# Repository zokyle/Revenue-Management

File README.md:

# Revenue-Management

Two independent FastAPI applications share this repository and its Python
dependencies:

| App | Directory | Run | What it does |
|-----|-----------|-----|--------------|
| Hotel revenue management | `app/` | `uvicorn app.main:app --reload` | demand forecasting, dynamic pricing, overbooking, PMS integrations |
| **Caddie** - golf strategy agent | `golf/` | `uvicorn golf.main:app --reload --port 8001` | learns your golf game from logged rounds and builds hole-by-hole strategies for any course, with the goal of breaking 80 |

```bash
pip install -r requirements.txt
cp .env.example .env
python scripts/seed_golf.py      # demo golfer, course and 12 rounds for the golf app
python -m pytest -q              # both apps' test suites
```

See [`golf/README.md`](golf/README.md) for how the golf agent works (with
pictures and analogies), the data-collection workflow, and the API.

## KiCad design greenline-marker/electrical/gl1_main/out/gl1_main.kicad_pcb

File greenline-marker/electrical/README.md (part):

# GL-1 electrical package

Nothing in this directory has been built or measured. The boards exist as design scripts,
KiCad 7 files generated from them and fabrication data that passed KiCad's DRC. Several
land patterns and pin tables are PROVISIONAL (list below): **do not order boards before
those are checked against the manufacturers' drawings.**

**Revision E (E-EVT1), 2026-11-18.** Both boards are rebuilt on revision E of
`design/master_params.yaml` and `design/DESIGN_SPEC.md` (amendments E24 to E28, E35, E36). No
part moved and no net changed on the main board: it was routed again from nothing because the
stored routing's fingerprint covers the revision stamp, and the copper came out identical to
revision D (2570 segments, 278 vias, compared item by item; `gl1_main/LAYOUT_LOG.md`, section
"Revision E"). The cradle board is 1.0 mm thick instead of 1.6 mm (E36). Both builds end with
the mechanical package's import check and both exit 0.

Revised before that on 2026-11-18 after three independent reviews of the first layout. What
changed then is in `gl1_main/LAYOUT_LOG.md` and in the design files under "REVIEW FIX".

## What is here

| Path | What |
|---|---|
| `tools/` | the in-house toolchain "gleda" 0.4.0: netlist as code, KiCad 7 board, router, KiCad DRC as the judge, outputs. Read `tools/README.md`, at least "Limitations" |
| `gl1_main/gl1_main_design.py` | main board: parts, nets, pin map, mechanical contract (from `design/master_params.yaml`), placement, router options |
| `gl1_main/build_gl1_main.py` | one command: checks, spec-rule table, pin-map check, board, route, KiCad DRC, outputs, schematic, mechanical import, quality figures, review renders -> `gl1_main/out/` |
| `gl1_main/build_netlist.py` | the earlier stage without copper -> `gl1_main/netlist_out/` |
| `gl1_main/check_netlist_rules.py`, `check_pinmap.py`, `pinmap.json` | specification -> netlist table with seeded-defect self-test; pin map against ST's open pin data; the exported pin map (a copy is in `out/`) |
| `gl1_main/routing.json` | the stored routing (reused when the design fingerprint matches; audited again on every build) |
| `gl1_main/NETLIST_NOTES.md`, `LAYOUT_LOG.md` | every value with its calculation, departures, PROVISIONAL list; every routing attempt |
| `gl1_main/layout_quality.py`, `layout_review.py`, `silk_text.py` | figures measured on the copper (the second file: the measurements the reviewers made, repeated by every build); silkscreen legend helper |
| `gl1_cradle/` | the cradle board, same structure (`gl1_cradle_design.py`, `build_gl1_cradle.py`, `build_netlist.py`, `check_cradle_rules.py`, `CRADLE_NOTES.md`, `make_usb_footprint.py`, `gl1_cradle_fp.pretty/`); its build also ends with the mechanical import (`board_import.py --cradle`) |

In each `out/`: `<name>.kicad_pcb / .kicad_pro / .kicad_dru`, `fab/` (Gerber X2, Excellon,
`README.txt` with stack-up, finish, via tenting and plugging) and `<name>-fab.zip`,
`assembly/` (position file, BOM, `<name>-bom-status.csv`, README) and `<name>-assembly.zip`,
`schematic/` (PDF, PNG,
netlist round trip), `<name>-mechanical.json`, `<name>-netlist.json`, `<name>-board.step`,
`renders/` and `review/` (PNG of every copper layer and both assembly sides), `drc.json`,
`layout_quality.md`, `build_summary.json`, `spec_rules.md`, `mechanical_import.txt`,
`outputs.json` (every output file with size and SHA-256; the build completes it with the status
BOM, the extended assembly README and the final assembly zip and then compares every entry
with the file on disk); for the main board also `pinmap.json`, `pinmap_check.txt`.

**The status BOM has two status columns.** "Status" follows `docs/SOURCING.md`: VERIFIED = a US
source listing this exact part number was seen on the date in the last column (listed for
sale; not a stock promise), PROVISIONAL = everything else; it is copied from the numbered row of
`docs/sourcing.csv` (main-NN / cradle-NN) that has the line's references, and it is PROVISIONAL
when that row names another part number or does not exist (the build then prints a WARNING and
counts the line under "sourcing rows out of step with the BOM"; today 0 on both boards).
"Design evidence" is RESEARCH or PROVISIONAL: how well the pin table, land pattern and values
of the line are known (with a note). Today every part number on both boards is VERIFIED as a
listing, while 31 of 37 main-board lines and 6 of 7 cradle lines are PROVISIONAL in their
design data. A line can be ordered only when both allow it. The remaining columns are the
sourcing risk, the alternates the sourcing report names (actions A4 and A18) and the sourcing
row. The alternates are CANDIDATES: the column is headed "candidates, NOT approved", each cell
says VERIFIED or PROVISIONAL for itself, and no alternate has been approved by anybody (the
microcontroller's cell, for instance, names a different MCU whose pin compatibility is from memory).

## Rebuild

Use the system interpreter (it has KiCad's `pcbnew`). Run from the `greenline-marker`
directory. `PINDATA` is a directory outside the repository holding ST's two open pin data
files (`STM32U585RITx.xml`, `GPIO-STM32U5x_gpio_v1_0_Modes.xml`); without `--pindata` the
pin-map check is PARTIAL.

```
/usr/bin/python3 -B electrical/gl1_main/build_netlist.py --pindata PINDATA      # exit 0, about 25 s
/usr/bin/python3 -B electrical/gl1_main/build_gl1_main.py --pindata PINDATA     # exit 0, about 60 s with the stored routing
/usr/bin/python3 -B electrical/gl1_main/build_gl1_main.py --pindata PINDATA --reroute   # exit 0; routes from nothing: about 6.5 min (router 328 s)
/usr/bin/python3 -B electrical/gl1_cradle/build_netlist.py                      # exit 0, about 5 s
/usr/bin/python3 -B electrical/gl1_cradle/build_gl1_cradle.py                   # exit 0, about 30 s
/usr/bin/python3 -B electrical/gl1_main/update_notes.py --check                 # exit 0
/usr/bin/python3 -I -B electrical/gl1_main/check_pinmap.py --selftest --pindata PINDATA   # exit 0
/usr/bin/python3 -B electrical/gl1_main/check_netlist_rules.py --selftest       # exit 0 (49 seeded defects)
/usr/bin/python3 -B electrical/gl1_cradle/check_cradle_rules.py --selftest      # exit 0 (18 seeded defects)
(cd mechanical && python3 -B cad/board_import.py ../electrical/gl1_main/out/gl1_main-mechanical.json)             # exit 0
(cd mechanical && python3 -B cad/board_import.py --cradle ../electrical/gl1_cradle/out/gl1_cradle-mechanical.json)   # exit 0
(cd design && python3 check_parts_vs_board.py)                                  # exit 0: the YAML part lists match the board
```

Exit status of both board builds: **0** only if every stage passed, the mechanical import
included; **1** for anything else. (At revision D the main build exited 2 because the import
failed on J1; that special status is gone with its cause.) The mechanical stage also fails if
the import warns that the board file is stamped with another revision than the YAML or states
another height-limit zone. The stored routing is reused only when its fingerprint matches the
design and the router options; the fingerprint covers the whole design dictionary, so ANY edit
of a design file, a status note or fab note included, makes the next build route again (about
5.5 min; the router is deterministic, so unchanged geometry gives the same copper). Times are
from a 4-core machine.

## Result (2026-11-18, revision E-EVT1)

| | Main board `gl1_main` | Cradle `gl1_cradle` |
|---|---|---|
| Size, layers | D shape R 21.1 mm, flat at y 17.3; 4 layers, 0.8 mm, ENIG | 30 x 22 mm, 2 layers, **1.0 mm** (E36; 0.91 mm core), ENIG |
| Parts | 121 (104 on the BOM: 103 fitted + R14 not fitted; 11 bare-copper footprints; 6 fiducials) | 20 (13 on the BOM: 10 fitted + 3 spring pins not fitted; 1 bare; 6 fiducials) |
| Nets | 95 | 10 |
| Toolchain checks | 0 errors, 2 warnings (`plane_partial` twice: the GND pours round the crystal and over the photodiode, intended) | 0 errors, 0 warnings |
| Rule table | 66 rows: 62 as specified, 4 departures, 0 open, 0 workarounds, 0 failed; self-test 49 of 49 seeded defects | 15 rows: 14 as specified, 1 departure (USB-C land), 0 failed; self-test 18 of 18 |
| Routed | 306 of 306 connections, audit clean; 278 vias, 2570 segments, 2297.4 mm; identical to the revision D copper | 29 of 29; 9 vias, 126.8 mm |
| KiCad DRC | 0 errors, 0 unconnected; 2 warnings, both cosmetic silkscreen (`silk_over_copper`, `silk_overlap`); nothing excluded, no rule relaxed. One rule ADDED by the build (zone clearance, see toolchain limits) | 0 errors, 0 unconnected; 1 `silk_overlap` warning |
| Rules | board minimum 0.100 / 0.100 mm (track / clearance); classes Default 0.15 / 0.127 mm, Power 0.30 / 0.127 mm (neck 0.15), Fine 0.10 / 0.10 mm and CamPower 0.15 / 0.10 mm, the last two fine only inside the two fine areas (pad field + 5 mm, 175 mm2, 13 % of the board; E35); via 0.50 / 0.25 mm through; copper to edge 0.30, hole to copper 0.20; layer 2 solid GND; vias tented on BOTH sides, plugging from the bottom in the fab notes | board minimum 0.127 / 0.127 mm; classes Default 0.20 / 0.15 mm and Power 0.40 / 0.15 mm; via 0.50 / 0.25 mm; copper to edge 0.30, hole to copper 0.20; spring-pin holes 0.80 mm finished |
| Fine track | 218.3 mm of 0.100 mm track on 28 nets: F.Cu 133.7, In2.Cu 31.8, B.Cu 52.8 mm; all inside the fine areas, farthest 5.3 mm from a ball field. As E35 allows; the fab README names F.Cu, In2.Cu and B.Cu for 0.100 / 0.100 mm | none |
| Outputs | 35 files in `outputs.json`, each equal to the file on disk; plotted data verified against the model; BOM 37 lines (Status 37 VERIFIED; design evidence 31 PROVISIONAL, 6 RESEARCH); 103 position rows; schematic 8 sheets, round trip equal (95 nets, 400 pads) | 29 files; BOM 7 lines (Status 7 VERIFIED; design evidence 6 PROVISIONAL, 1 RESEARCH); schematic 3 sheets, round trip equal |
| Mechanical import | **passes, exit 0, no warning**: outline, hole and slot; 86 top-side parts 0.25 mm or more from the tub; J1 body box and anchor on the YAML (mouth y -17.3); the battery keep-out equals `battery.body` less the YAML notch; 18 bottom-side parts in the openings; 14 copper-only footprints by their own rules; 7 pads on the pin axes | **passes, exit 0** (`--cradle`, new at revision E): thickness 1.0, outline, four screw holes, seven pins on the pad row and on the modelled axes (4 fitted), receptacle on the modelled one, nothing else on the top face |

Main-board figures (`gl1_main/out/layout_quality.md`, measured by the build on the DRC'd board):

* Camera bus after the series arrays: 577 mm of track for 293 mm of spanning trees (x1.97),
  48 vias. This is WORSE than the first layout (449 mm).
* Camera data against PCLK, ball to MCU pad: left camera PCLK is the longest line (99.5 mm)
  and the data lines are 27 to 84 mm shorter (-589 to -188 ps at 7 ps/mm); right camera
  -9.7 to +77.5 mm (-68 to +542 ps); the longest line is 105 mm. The pixel clock is 12 MHz
  (period 83 ns), so the skew is under 1 % of a period; the copper is long all the same.
* Camera supply balls to the nearest capacitor of the net, along the copper: U2 DOVDD 9.9 mm,
  U2 AVDD 5.9 mm, U2 DVDD 4.2 mm, U3 DOVDD 5.0 mm, U3 AVDD 7.7 mm, U3 DVDD 7.1 mm.
* Smallest via-to-pad gap on the top side 0.100 mm (own net, vias tented), 0.134 mm to a pad
  of another net (rule 0.127). Smallest solder-mask web: top 0.150 mm (two IMU pads),
  bottom 0.360 mm. No via opening in either mask.
* Copper to the board edge (outline and the routed locating slot; rule 0.30): 0.325 mm routed
  (CAM_D3, at the slot), 0.355 mm pads (R4, at the slot). Copper to the wall of the drilled
  locating hole H1 (a separate rule, 0.20): 0.321 mm routed (CAM_D4), 0.795 mm pads. Earlier
  issues gave the 0.321 mm as an edge distance; the figures are now reported separately by
  `layout_quality.py`.
* Plane clearance: 0.200 mm to every foreign track and via on all four filled layers.
* Layer 3 (In2.Cu): V2V8 fill on 59.0 % of the board in 4 pieces, 461 mm of signal track;
  408 of 888 mm of bottom-layer track (46 %) has no In2 copper above it. It is a supply fill
  and a routing layer, not a plane. Layer 2: GND fill 86.0 %, one piece, no track.
* IMU: no copper in the top-layer rule area under the body, no via within 0.35 mm of the
  body outline; a CP1_MCU track clips the corner of the body outline by 0.03 mm; 12.3 mm or
  more from every regulator, 26 mm from the charger. U4 stands at 90 degrees (see "What the
  firmware must take from this board").
* Crystal: 7.6 and 4.8 mm, top layer only, no via; in its no-via box only a GND via and
  R1's V2V8 via; nearest foreign via 0.275 mm (CAM_EN, static); nearest foreign top-layer
  track 0.168 mm (VBUS_SENSE at the neighbouring MCU pad, static); layer 2 unbroken under
  it; tracks of other nets run below that plane on layers 3 and 4.
* PD_K: 33.6 mm (28.2 on the bottom layer, links between the seven cathode pads included),
  1 via; no LED, clock or bus track within 0.5 mm on its layer; on layer 3 CAM_HREF, CP3,
  CP4 and LCD_DISP cross over it (2.0 / 2.2 / 0.3 / 1.2 mm).
* Vias: 278, 37 of them under the cell, all tented on both sides.
* USB pair: D- 41.7 mm, D+ 41.2 mm, 6 and 2 vias, up to 13.6 mm apart. NOT a coupled pair.

## Departures from the specification and from the YAML

Closed at revision E, and therefore gone from this table: J1's position (E24 is in the YAML),
the notch in the battery keep-out (YAML `battery.board_keepout_notch`), the fine class on three
layers (E35), the cradle pin tail against the board thickness (E36).

| What | Numbers |
|---|---|
| CamPower | a second class, 0.15 / 0.10 mm, for the camera supply balls, inside the same fine areas (in no amendment) |
| vias tented on both sides | the specification asks for the underside only; the top is tented as well because the cell lies on it |
| TP5 | a fifth test pad (VDDUSB) beyond the four of E4 (the YAML lists it because it is on the board, flagged open) |
| cradle fuse trip current | 0.75 A against E6's "about 0.5 A" (hold 0.35 A and 1.0 ohm are inside E25) |
| cradle USB-C land | the four outer ground pads (two lands) are 1.11 mm long, 0.04 mm shorter than the 1.15 mm of KiCad's pattern (hole clearance 0.20 mm) |
| carried from the netlist | cam 2d, grain c, grain d (`gl1_main/out/spec_rules.md`). Rows "rail VDDUSB" and "E1 b" were counted here until the final audit: their 2.2 uF capacitors are the letter of the rev E spec (E27), and the rows now quote that text and test for 2.2 uF |

## Known weaknesses of this layout (review findings that are NOT fixed)

* **Camera supply decoupling.** The reviewers asked for a 100 nF within about 2 mm of every
  supply ball. Twenty-three routing variants with capacitors 1.45 mm beside the balls ended
  at 97.4 to 99.3 %. The paths are 4.2 to 9.9 mm (above). The left camera's DOVDD ball, the
  worst case of the first layout (15.6 mm), is at 9.9 mm. To be done again with the real
  ball map, by hand if the router cannot.
* **PD_K** has a ground pour beside it, not a VBIAS guard, and four nets cross it on layer 3.
* **Layer 3 is not a plane**; nearly half of the bottom-layer track has no reference on the
  adjacent layer. No ground stitching vias at layer changes (the router has none).
* **Long camera lines** (above). PCLK of the left camera is 99.5 mm.
* **SWDIO, SWCLK and NRST** go from the underside pads to the MCU with no clamp and no series
  resistor; NRST's 100 nF is at the MCU. The specification names only VBUS, D+ and D- for
  the clamp: a specification gap, recorded as an EVT limitation (the three pads belong in the
  ESD test plan).
* **Bring-up access**: BOOT0 has no pad (first programming is SWD through the factory
  fixture); the seven pads carry no always-on rail and the cradle's J2 no reference voltage;
  a board without its cell gets at most the charger's 20 mA in the cradle.
* No reference designators on the silkscreen; use the assembly renders and position file.
* The router does no length matching, no guard traces and no differential pairs.

## What the firmware must take from this board

`gl1_main/pinmap.json` (copy in `gl1_main/out/`) is the single input of
`firmware/tools/gen_pins.py`. **Revision E changed no pin.** The board build left the file
byte-identical (SHA-256 d33ff53f...3972e4); the final audit of rev E then corrected two TEXTS in it
and nothing else: the `spec` string ("DESIGN_SPEC rev E (EVT1) with amendments E1 to E36 (in the
netlist and on the board: E1 to E4, E24 to E28 and E35)"; it said rev D, E1 to E34) and the first
open item for the firmware (the IMU axis map is generated now; see below). The file is now SHA-256
30505550677ba2dca446e0d2cf8f66e4ea720316e02fde1aa317bb97d4d0371f; `make pins` was run in
`firmware/` in the same step and `make pins-check` passes (the generated header changed in its
hash and comment lines only). A key-by-key comparison of the two JSON files shows no other difference.

* `firmware_notes` (17): unchanged in number; notes 2 and 4 no longer claim outstanding work.
* `imu_mounting`: **U4 is at 90 degrees counter-clockwise seen from above.** Marker X =
  -sensor Y, marker Y = +sensor X, Z unchanged, i.e. `GL_PROV_IMU_MARKER_X_AXIS 1 / SIGN -1`,
  `Y_AXIS 0 / SIGN +1` (the key names in the pin map are historical). The firmware took this up
  in its phase 3: the identity placeholder of `firmware/core/gl_provisional.h` is gone and
  `gen_pins.py` writes the map into `gl_pins.h` as `GL_PINS_IMU_MARKER_*`. PROVISIONAL: the map
  assumes ST's axis drawing matches KiCad's LGA-14 pattern at rotation 0 (not read).
* `open_items_for_firmware` (4): the IMU axes; ship mode with PB5 / PB14 floating (possible
  27 uA through R13 if the UCPD dead-battery switch acts in Shutdown, PROVISIONAL, RM0456 not
  read); first programming by SWD only; no ESD parts on the three service pads. These are
  not `firmware_notes` because `gen_pins.py` accepts only notes it has a rule for.

## PROVISIONAL items that gate ordering boards

Each is isolated in one marked table of its design file.

| Item | Where | Risk if wrong |
|---|---|---|
| OVM7692 ball map, pitch 0.5 mm, pad 0.20 mm (stand-in) | `OVM7692_BALLS` | both cameras mis-wired; array order, fan-out and capacitor placement must be redone |
| Camera image orientation: which package side carries the 640-pixel axis (spec section 7 gate). Both cameras stand at rotation 0 with the 3.47 mm side along x, which assumes it | placement of U2 / U3 | images rotated by 90 degrees; the horizontal field is the short one |
| BQ25101YFP ball map and 0.23 mm lands | `BQ25101_BALLS` | charger mis-wired |
| LCD tail pin order and which tail edge is pin 1 | `LCD_TAIL`, `LCD_TAIL_PIN1_EDGE` | all ten display pins mirrored |
| LM66100DCKR pin table and CE polarity (from memory, E25) | `LM66100_PINS` | VBUS switch mis-wired |
| VEMD8080 land pattern | `VEMD8080_PADS` | photodiode does not fit |
| FH12A numbering equal to the FH12 land pattern and its 2.0 mm height (sourcing A15); the tail fold behind J1's mouth (Sharp drawing; the YAML zone is `basis: provisional`) | design file, section 1; YAML `tub_keepouts.lcd_tail` | connector mirrored / tail fold does not fit |
| IMU axis map (above) | `pinmap.json` `imu_mounting` | slope direction wrong by 90 degrees |
| Cell lead polarity and position: BT1 = VBAT at (-18.4, -2.7), BT2 = GND at (-18.4, -5.8). No source says which lead of GM201030-PCB is where | `battery_pad_positions()` | cell connected reversed, or the leads cross |
| Generic KiCad 0402 LED land pattern and its polarity mark for VLMS1500 and SFH 4053B (pad 1 taken as the cathode) | `led_positions()` | all 16 LEDs reversed |
| ABS07 crystal on the Epson FC-135 land pattern | part Y1 | crystal does not seat |
| Mill-Max 0914: tail 0.635 mm, hole 0.80 mm, **tail length about 1.34 mm** (search extracts and a subtraction, not the drawing). E36 made the board 1.0 mm so that this tail comes 0.34 mm through; if the real tail is shorter than 1.2 mm the joint has no fillet again | cradle `MILLMAX_0914`, YAML `cradle.pins.tail_length` | pins cannot be soldered properly |
| Cradle fuse (listing data), screw hole and head, USB-C land (four outer ground pads 1.11 mm, 0.04 mm shorter than KiCad's) | cradle `PTC`, `make_usb_footprint.py` | charger input headroom; fit |
| 0.100 / 0.100 mm inside the fine areas on F.Cu, In2.Cu and B.Cu accepted by the fabricator in writing (spec E7 as widened by E35: the quote request must name all three layers); 0.25 mm as the DRILL size on a 0.50 mm pad (finished about 0.20 mm) | fab README | board cannot be made as drawn; ring 0.075 to 0.10 mm if 0.25 is read as the finished hole |
| Every passive order code, MCU electrical limits, ROM bootloader pin list, LP5907 enable current, MLCC bias derating (the 1 uF and 2.2 uF parts are new: sourcing A3) | `NETLIST_NOTES.md` sections 6 and 7, BOM column "Design evidence" | see notes |

**Sourcing actions of `docs/SOURCING.md` section 12** (the full table, action by action, is in
`gl1_main/NETLIST_NOTES.md` section 12):

* **Applied in the design files and BOMs** (same footprint, same value): A1 (1 uF: Samsung
  CL05A105KP5NNNC for the obsolete GRM155R61A105KE15D), A2 (2.2 uF: GRM155R61A225KE01D, second
  source CL05A225KP5NSNC), A4 (alternate CL05B104KO5NNNC for the 100 nF line, both BOMs), A5
  (cradle fuse 0603L035YR), A6 (spring-pin tail and hole diameter; the tail length is answered
  by E36), A7 (U12 LM66100DCKR, Digi-Key 296-53541-1-ND), A8 (U11 LP5907MFX-3.3/NOPB), A9
  (SFH 4053B kept, IN-S42CTQIR named), A13 (U4 from Newark at 5.75), A17 (order codes and
  prices; the cradle's R1 / R2 and C1 codes were entered at this revision), A18 (the
  alternates column: candidates, none approved).
* **Open, needs an owner decision or a document this session could not read:** A3 (DC-bias
  curves of the 1 uF, 2.2 uF and 4.7 uF parts; a larger case would be a footprint change), A8's
  order code (the live US distributor page), A9 (SFH 4053B data sheet: wavelength, package,
  polarity mark), A11 / A12 (the display LS013B7DH03 and the cell GM201030-PCB are not board
  parts; the main assembly README names them as off-board items, but the purchasing list above
  the BOMs has no file and no owner here), A14 (flash on tray or reel: with the assembler), A15
  (FH12A against the FH12 land pattern: Hirose drawing), A5's 1206 fallback fuse and E6's trip
  current (spec owner).
* **Not design-file changes:** A10 (camera life cycle and quotes), A16 (MCU price and lead
  time). **Not electrical:** A19 to A35.
* The availability doubts stay visible on the status BOM (OVM7692-RYAA high; SFH 4053B medium
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
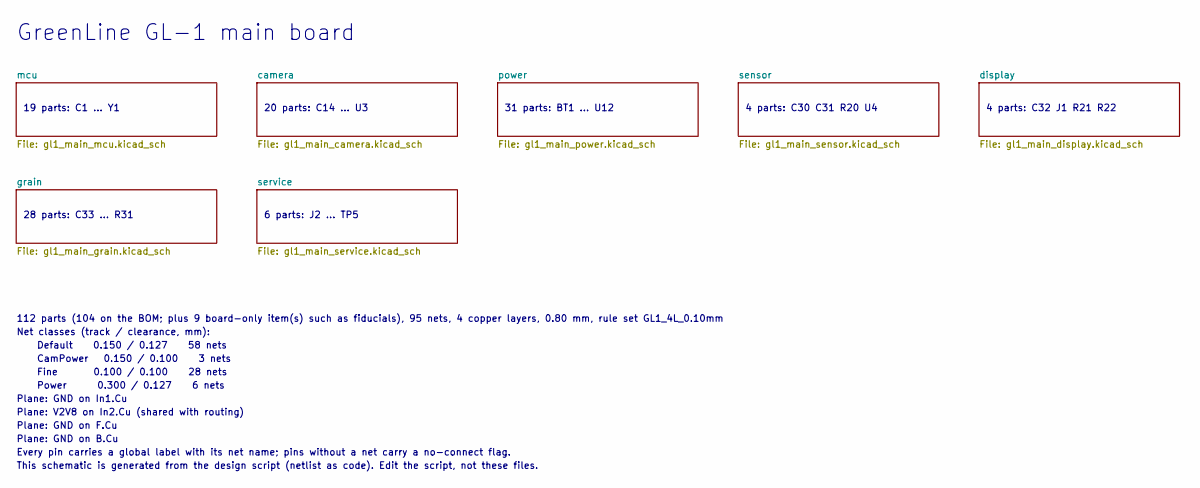
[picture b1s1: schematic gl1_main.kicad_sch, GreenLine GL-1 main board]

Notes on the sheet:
GreenLine GL-1 main board
19 parts: C1 ... Y1
20 parts: C14 ... U3
31 parts: BT1 ... U12
4 parts: C30 C31 R20 U4
4 parts: C32 J1 R21 R22
28 parts: C33 ... R31
6 parts: J2 ... TP5
112 parts (104 on the BOM; plus 9 board-only item(s) such as fiducials), 95 nets, 4 copper layers, 0.80 mm, rule set GL1_4L_0.10mm
Net classes (track / clearance, mm):
Default 0.150 / 0.127 58 nets
CamPower 0.150 / 0.100 3 nets
Fine 0.100 / 0.100 28 nets
Power 0.300 / 0.127 6 nets
Plane: GND on In1.Cu
Plane: V2V8 on In2.Cu (shared with routing)
Plane: GND on F.Cu
Plane: GND on B.Cu
Every pin carries a global label with its net name; pins without a net carry a no-connect flag.
This schematic is generated from the design script (netlist as code). Edit the script, not these files.

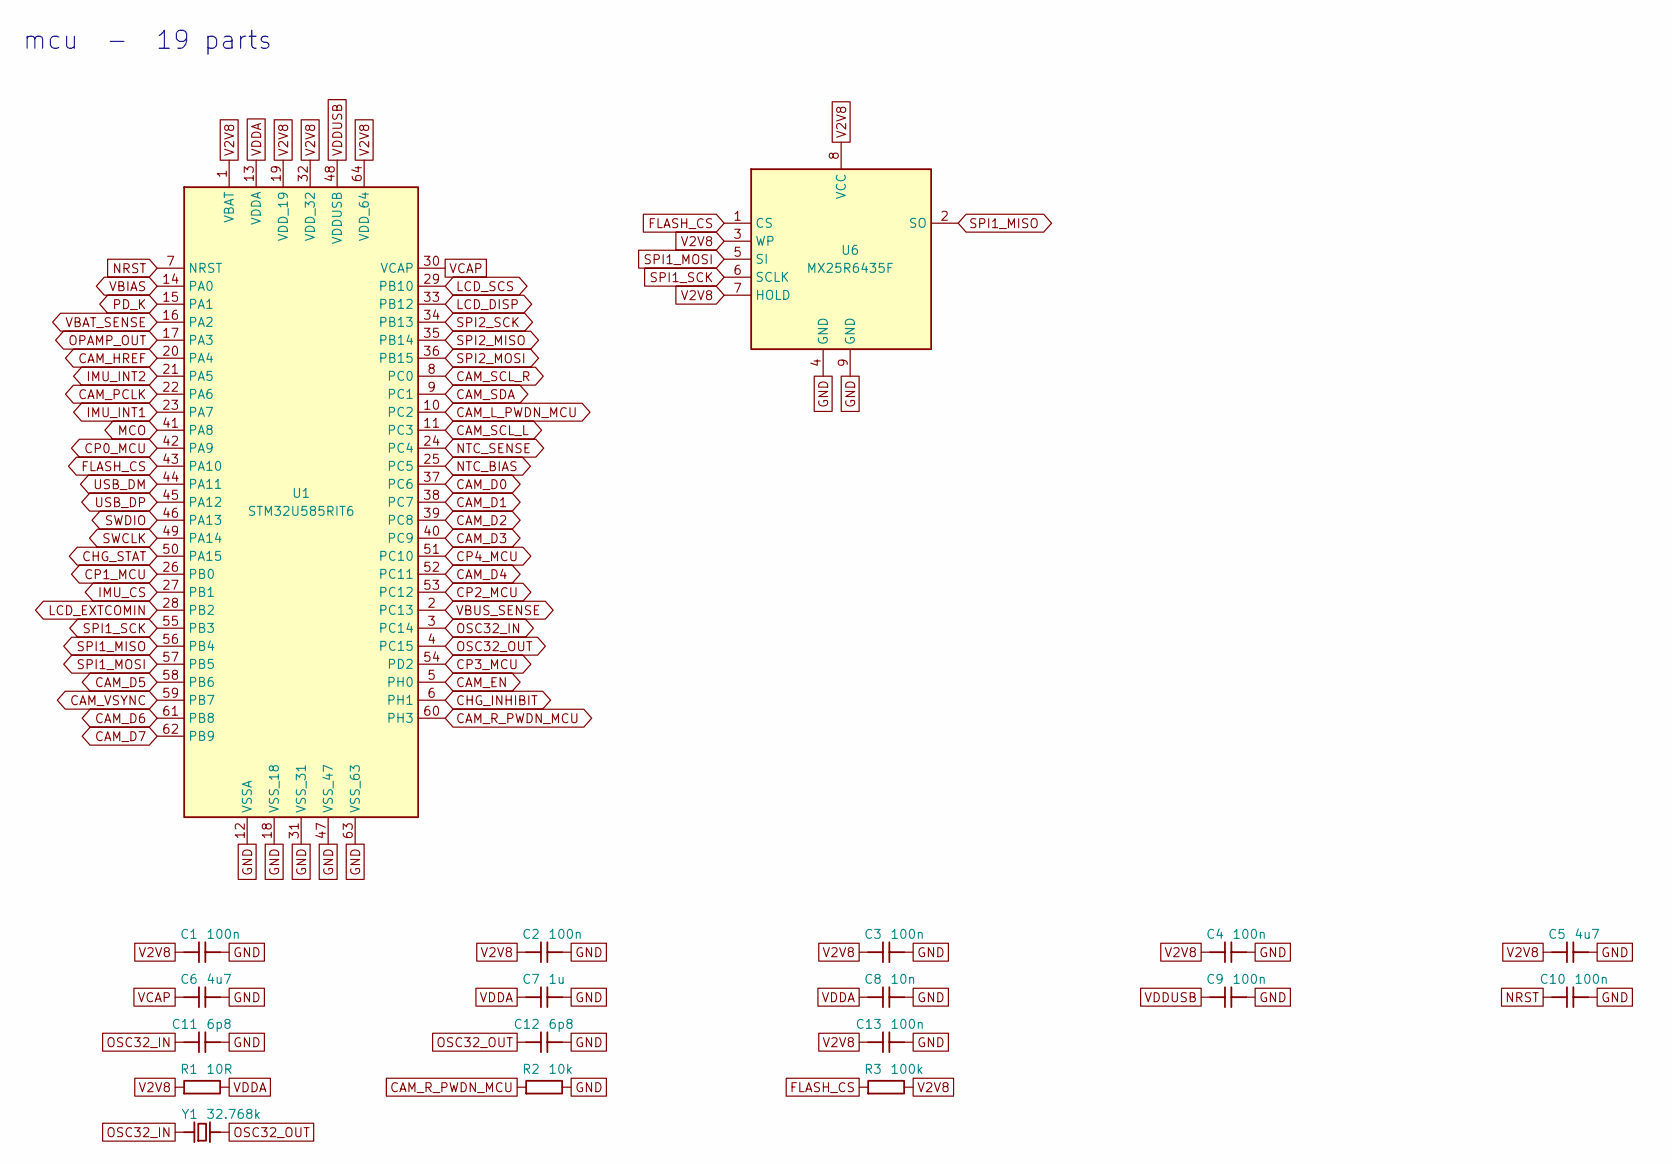
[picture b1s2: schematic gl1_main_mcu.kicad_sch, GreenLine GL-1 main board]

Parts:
C1, C2, C3, C4, C9, C10, C13: 100n; C_0402_1005Metric; MPN GRM155R71C104KA88D
C5, C6: 4u7; C_0402_1005Metric; MPN GRM155R60J475ME47D
C7: 1u; C_0402_1005Metric; MPN CL05A105KP5NNNC
C8: 10n; C_0402_1005Metric; MPN GRM155R71H103KA88D
C11, C12: 6p8; C_0402_1005Metric; MPN GRM1555C1H6R8CA01D
R1: 10R; R_0402_1005Metric; MPN RC0402FR-0710RL
R2: 10k; R_0402_1005Metric; MPN RC0402FR-0710KL
R3: 100k; R_0402_1005Metric; MPN RC0402FR-07100KL
U1: STM32U585RIT6; LQFP-64_10x10mm_P0.5mm; MPN STM32U585RIT6
U6: MX25R6435F; WSON-8-1EP_6x5mm_P1.27mm_EP3.4x4mm; MPN MX25R6435FZNIL0
Y1: 32.768k; Crystal_SMD_3215-2Pin_3.2x1.5mm; MPN ABS07-120-32.768KHZ-T

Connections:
CAM_D0: U1.37 (PC6); also elsewhere on the board
CAM_D1: U1.38 (PC7); also elsewhere on the board
CAM_D2: U1.39 (PC8); also elsewhere on the board
CAM_D3: U1.40 (PC9); also elsewhere on the board
CAM_D4: U1.52 (PC11); also elsewhere on the board
CAM_D5: U1.58 (PB6); also elsewhere on the board
CAM_D6: U1.61 (PB8); also elsewhere on the board
CAM_D7: U1.62 (PB9); also elsewhere on the board
CAM_EN: U1.5 (PH0); also elsewhere on the board
CAM_HREF: U1.20 (PA4); also elsewhere on the board
CAM_L_PWDN_MCU: U1.10 (PC2); also elsewhere on the board
CAM_PCLK: U1.22 (PA6); also elsewhere on the board
CAM_R_PWDN_MCU: R2.1, U1.60 (PH3); also elsewhere on the board
CAM_SCL_L: U1.11 (PC3); also elsewhere on the board
CAM_SCL_R: U1.8 (PC0); also elsewhere on the board
CAM_SDA: U1.9 (PC1); also elsewhere on the board
CAM_VSYNC: U1.59 (PB7); also elsewhere on the board
CHG_INHIBIT: U1.6 (PH1); also elsewhere on the board
CHG_STAT: U1.50 (PA15); also elsewhere on the board
CP0_MCU: U1.42 (PA9); also elsewhere on the board
CP1_MCU: U1.26 (PB0); also elsewhere on the board
CP2_MCU: U1.53 (PC12); also elsewhere on the board
CP3_MCU: U1.54 (PD2); also elsewhere on the board
CP4_MCU: U1.51 (PC10); also elsewhere on the board
FLASH_CS: R3.1, U1.43 (PA10), U6.1 (CS)
GND: C1.2, C2.2, C3.2, C4.2, C5.2, C6.2, C7.2, C8.2, C9.2, C10.2, C11.2, C12.2, C13.2, R2.2, U1.12 (VSSA), U1.18 (VSS_18), U1.31 (VSS_31), U1.47 (VSS_47), U1.63 (VSS_63), U6.4 (GND), U6.9 (GND); also elsewhere on the board
IMU_CS: U1.27 (PB1); also elsewhere on the board
IMU_INT1: U1.23 (PA7); also elsewhere on the board
IMU_INT2: U1.21 (PA5); also elsewhere on the board
LCD_DISP: U1.33 (PB12); also elsewhere on the board
LCD_EXTCOMIN: U1.28 (PB2); also elsewhere on the board
LCD_SCS: U1.29 (PB10); also elsewhere on the board
MCO: U1.41 (PA8); also elsewhere on the board
NRST: C10.1, U1.7 (NRST); also elsewhere on the board
NTC_BIAS: U1.25 (PC5); also elsewhere on the board
NTC_SENSE: U1.24 (PC4); also elsewhere on the board
OPAMP_OUT: U1.17 (PA3); also elsewhere on the board
OSC32_IN: C11.1, U1.3 (PC14), Y1.1
OSC32_OUT: C12.1, U1.4 (PC15), Y1.2
PD_K: U1.15 (PA1); also elsewhere on the board
SPI1_MISO: U1.56 (PB4), U6.2 (SO)
SPI1_MOSI: U1.57 (PB5), U6.5 (SI); also elsewhere on the board
SPI1_SCK: U1.55 (PB3), U6.6 (SCLK); also elsewhere on the board
SPI2_MISO: U1.35 (PB14); also elsewhere on the board
SPI2_MOSI: U1.36 (PB15); also elsewhere on the board
SPI2_SCK: U1.34 (PB13); also elsewhere on the board
SWCLK: U1.49 (PA14); also elsewhere on the board
SWDIO: U1.46 (PA13); also elsewhere on the board
USB_DM: U1.44 (PA11); also elsewhere on the board
USB_DP: U1.45 (PA12); also elsewhere on the board
V2V8: C1.1, C2.1, C3.1, C4.1, C5.1, C13.1, R1.1, R3.2, U1.1 (VBAT), U1.19 (VDD_19), U1.32 (VDD_32), U1.64 (VDD_64), U6.3 (WP), U6.7 (HOLD), U6.8 (VCC); also elsewhere on the board
VBAT_SENSE: U1.16 (PA2); also elsewhere on the board
VBIAS: U1.14 (PA0); also elsewhere on the board
VBUS_SENSE: U1.2 (PC13); also elsewhere on the board
VCAP: C6.1, U1.30 (VCAP)
VDDA: C7.1, C8.1, R1.2, U1.13 (VDDA)
VDDUSB: C9.1, U1.48 (VDDUSB); also elsewhere on the board

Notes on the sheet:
mcu - 19 parts

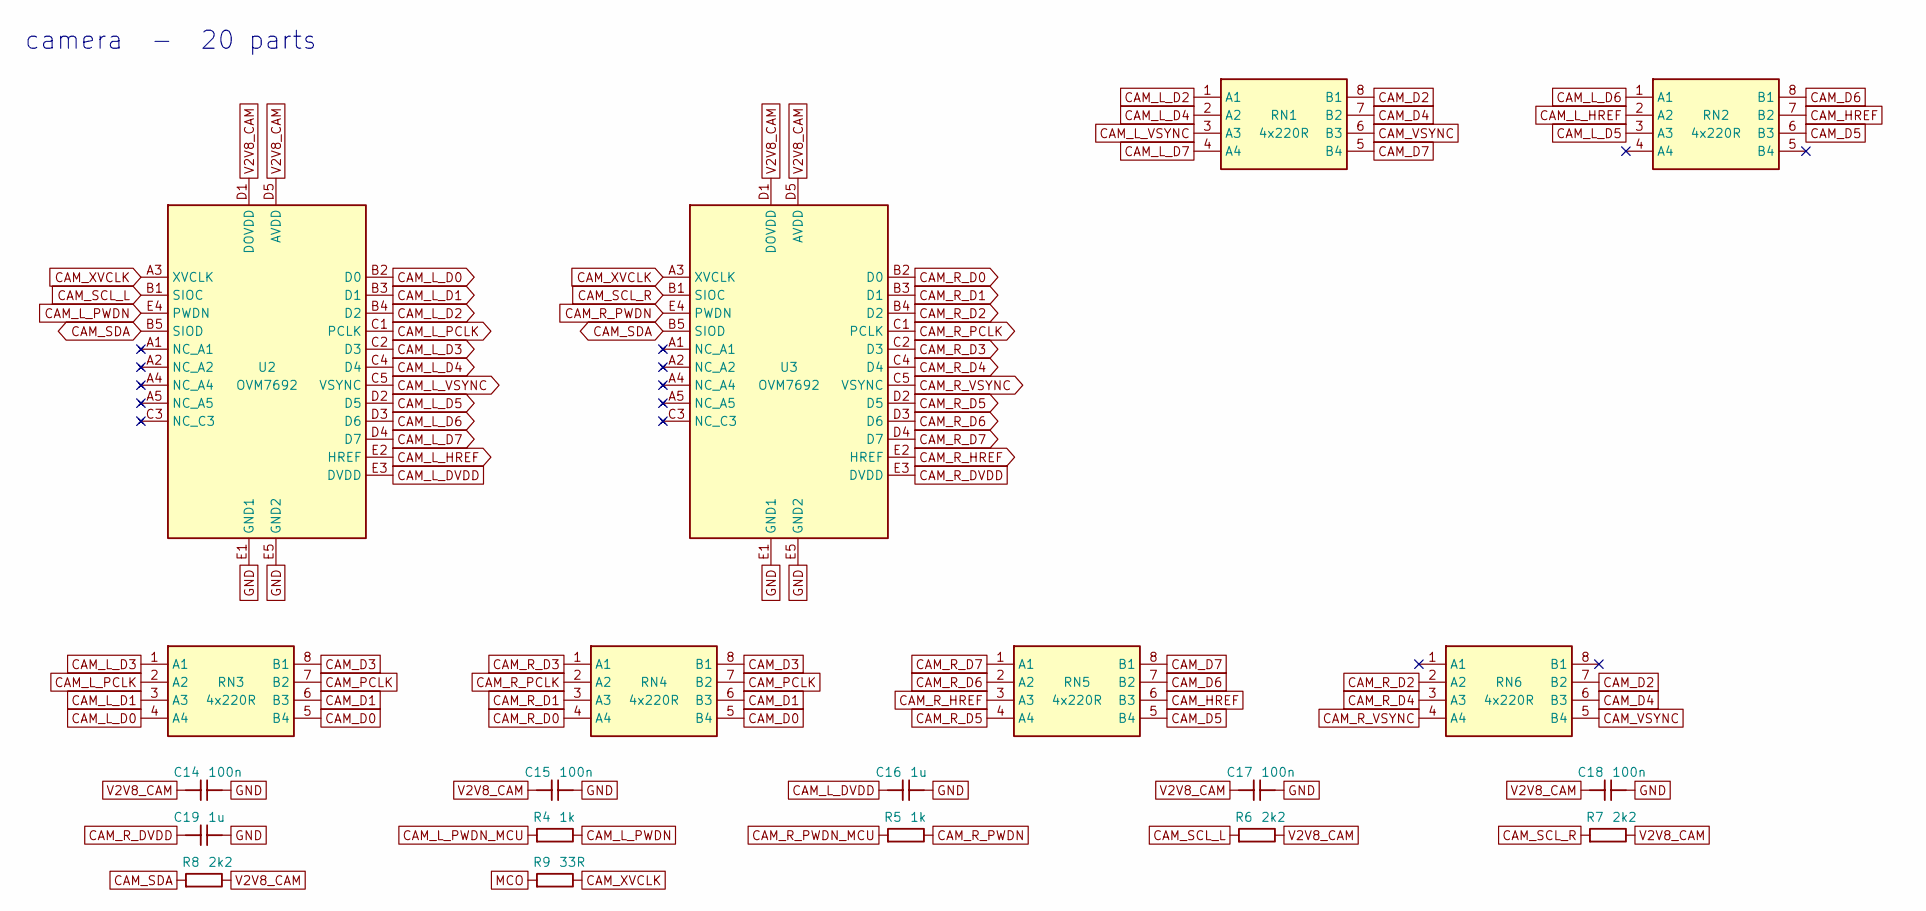
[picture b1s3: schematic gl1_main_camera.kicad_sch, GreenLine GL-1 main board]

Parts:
C14, C15, C17, C18: 100n; C_0402_1005Metric; MPN GRM155R71C104KA88D
C16, C19: 1u; C_0402_1005Metric; MPN CL05A105KP5NNNC
R4, R5: 1k; R_0402_1005Metric; MPN RC0402FR-071KL
R6, R7, R8: 2k2; R_0402_1005Metric; MPN RC0402FR-072K2L
R9: 33R; R_0402_1005Metric; MPN RC0402FR-0733RL
RN1, RN2, RN3, RN4, RN5, RN6: 4x220R; R_Array_Convex_4x0402; MPN EXB-28V221JX
U2, U3: OVM7692; OVM7692_BGA25_P0.5_PROVISIONAL; MPN OVM7692-RYAA

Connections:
CAM_D0: RN3.5 (B4), RN4.5 (B4); also elsewhere on the board
CAM_D1: RN3.6 (B3), RN4.6 (B3); also elsewhere on the board
CAM_D2: RN1.8 (B1), RN6.7 (B2); also elsewhere on the board
CAM_D3: RN3.8 (B1), RN4.8 (B1); also elsewhere on the board
CAM_D4: RN1.7 (B2), RN6.6 (B3); also elsewhere on the board
CAM_D5: RN2.6 (B3), RN5.5 (B4); also elsewhere on the board
CAM_D6: RN2.8 (B1), RN5.7 (B2); also elsewhere on the board
CAM_D7: RN1.5 (B4), RN5.8 (B1); also elsewhere on the board
CAM_HREF: RN2.7 (B2), RN5.6 (B3); also elsewhere on the board
CAM_L_D0: RN3.4 (A4), U2.B2 (D0)
CAM_L_D1: RN3.3 (A3), U2.B3 (D1)
CAM_L_D2: RN1.1 (A1), U2.B4 (D2)
CAM_L_D3: RN3.1 (A1), U2.C2 (D3)
CAM_L_D4: RN1.2 (A2), U2.C4 (D4)
CAM_L_D5: RN2.3 (A3), U2.D2 (D5)
CAM_L_D6: RN2.1 (A1), U2.D3 (D6)
CAM_L_D7: RN1.4 (A4), U2.D4 (D7)
CAM_L_DVDD: C16.1, U2.E3 (DVDD)
CAM_L_HREF: RN2.2 (A2), U2.E2 (HREF)
CAM_L_PCLK: RN3.2 (A2), U2.C1 (PCLK)
CAM_L_PWDN: R4.2, U2.E4 (PWDN)
CAM_L_PWDN_MCU: R4.1; also elsewhere on the board
CAM_L_VSYNC: RN1.3 (A3), U2.C5 (VSYNC)
CAM_PCLK: RN3.7 (B2), RN4.7 (B2); also elsewhere on the board
CAM_R_D0: RN4.4 (A4), U3.B2 (D0)
CAM_R_D1: RN4.3 (A3), U3.B3 (D1)
CAM_R_D2: RN6.2 (A2), U3.B4 (D2)
CAM_R_D3: RN4.1 (A1), U3.C2 (D3)
CAM_R_D4: RN6.3 (A3), U3.C4 (D4)
CAM_R_D5: RN5.4 (A4), U3.D2 (D5)
CAM_R_D6: RN5.2 (A2), U3.D3 (D6)
CAM_R_D7: RN5.1 (A1), U3.D4 (D7)
CAM_R_DVDD: C19.1, U3.E3 (DVDD)
CAM_R_HREF: RN5.3 (A3), U3.E2 (HREF)
CAM_R_PCLK: RN4.2 (A2), U3.C1 (PCLK)
CAM_R_PWDN: R5.2, U3.E4 (PWDN)
CAM_R_PWDN_MCU: R5.1; also elsewhere on the board
CAM_R_VSYNC: RN6.4 (A4), U3.C5 (VSYNC)
CAM_SCL_L: R6.1, U2.B1 (SIOC); also elsewhere on the board
CAM_SCL_R: R7.1, U3.B1 (SIOC); also elsewhere on the board
CAM_SDA: R8.1, U2.B5 (SIOD), U3.B5 (SIOD); also elsewhere on the board
CAM_VSYNC: RN1.6 (B3), RN6.5 (B4); also elsewhere on the board
CAM_XVCLK: R9.2, U2.A3 (XVCLK), U3.A3 (XVCLK)
GND: C14.2, C15.2, C16.2, C17.2, C18.2, C19.2, U2.E1 (GND1), U2.E5 (GND2), U3.E1 (GND1), U3.E5 (GND2); also elsewhere on the board
MCO: R9.1; also elsewhere on the board
V2V8_CAM: C14.1, C15.1, C17.1, C18.1, R6.2, R7.2, R8.2, U2.D1 (DOVDD), U2.D5 (AVDD), U3.D1 (DOVDD), U3.D5 (AVDD); also elsewhere on the board

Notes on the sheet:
camera - 20 parts

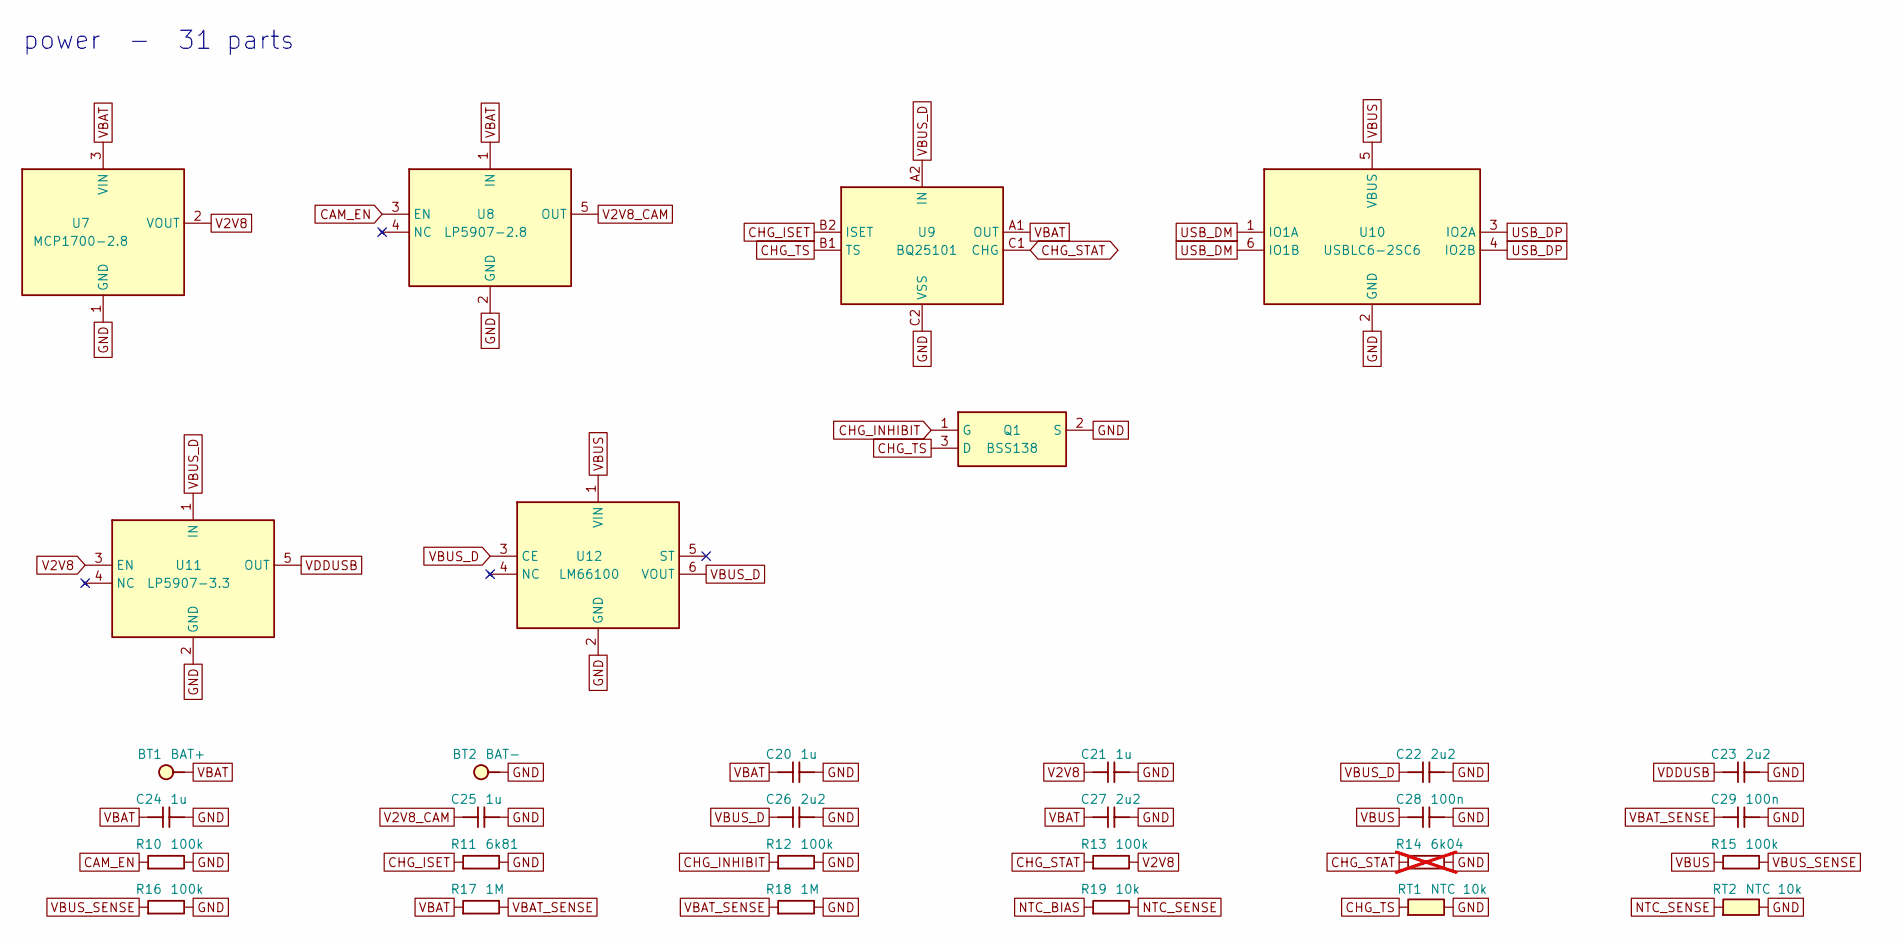
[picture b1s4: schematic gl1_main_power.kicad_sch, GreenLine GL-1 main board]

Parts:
BT1: BAT+; BatteryTab_1.5x2.4mm
BT2: BAT-; BatteryTab_1.5x2.4mm
C20, C21, C24, C25: 1u; C_0402_1005Metric; MPN CL05A105KP5NNNC
C22, C23, C26, C27: 2u2; C_0402_1005Metric; MPN GRM155R61A225KE01D
C28, C29: 100n; C_0402_1005Metric; MPN GRM155R71C104KA88D
Q1: BSS138; SOT-23; MPN BSS138LT1G
R10, R12, R13, R15, R16: 100k; R_0402_1005Metric; MPN RC0402FR-07100KL
R11: 6k81; R_0402_1005Metric; MPN RC0402FR-076K81L
R14: 6k04; R_0402_1005Metric; MPN RC0402FR-076K04L; not fitted
R17, R18: 1M; R_0402_1005Metric; MPN RC0402FR-071ML
R19: 10k; R_0402_1005Metric; MPN RC0402FR-0710KL
RT1, RT2: NTC 10k; R_0402_1005Metric; MPN NCU15XH103F60RC
U7: MCP1700-2.8; SOT-23; MPN MCP1700T-2802E/TT
U8: LP5907-2.8; SOT-23-5; MPN LP5907MFX-2.8/NOPB
U9: BQ25101; BQ25101_YFP_DSBGA6_P0.4_PROVISIONAL; MPN BQ25101YFPR
U10: USBLC6-2SC6; SOT-23-6; MPN USBLC6-2SC6
U11: LP5907-3.3; SOT-23-5; MPN LP5907MFX-3.3/NOPB
U12: LM66100; SOT-363_SC-70-6; MPN LM66100DCKR

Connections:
CAM_EN: R10.1, U8.3 (EN); also elsewhere on the board
CHG_INHIBIT: Q1.1 (G), R12.1; also elsewhere on the board
CHG_ISET: R11.1, U9.B2 (ISET)
CHG_STAT: R13.1, R14.1, U9.C1 (CHG); also elsewhere on the board
CHG_TS: Q1.3 (D), RT1.1, U9.B1 (TS)
GND: BT2.1, C20.2, C21.2, C22.2, C23.2, C24.2, C25.2, C26.2, C27.2, C28.2, C29.2, Q1.2 (S), R10.2, R11.2, R12.2, R14.2, R16.2, R18.2, RT1.2, RT2.2, U7.1 (GND), U8.2 (GND), U9.C2 (VSS), U10.2 (GND), U11.2 (GND), U12.2 (GND); also elsewhere on the board
NTC_BIAS: R19.1; also elsewhere on the board
NTC_SENSE: R19.2, RT2.1; also elsewhere on the board
USB_DM: U10.1 (IO1A), U10.6 (IO1B); also elsewhere on the board
USB_DP: U10.3 (IO2A), U10.4 (IO2B); also elsewhere on the board
V2V8: C21.1, R13.2, U7.2 (VOUT), U11.3 (EN); also elsewhere on the board
V2V8_CAM: C25.1, U8.5 (OUT); also elsewhere on the board
VBAT: BT1.1, C20.1, C24.1, C27.1, R17.1, U7.3 (VIN), U8.1 (IN), U9.A1 (OUT); also elsewhere on the board
VBAT_SENSE: C29.1, R17.2, R18.1; also elsewhere on the board
VBUS: C28.1, R15.1, U10.5 (VBUS), U12.1 (VIN); also elsewhere on the board
VBUS_D: C22.1, C26.1, U9.A2 (IN), U11.1 (IN), U12.3 (CE), U12.6 (VOUT)
VBUS_SENSE: R15.2, R16.1; also elsewhere on the board
VDDUSB: C23.1, U11.5 (OUT); also elsewhere on the board

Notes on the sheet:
power - 31 parts

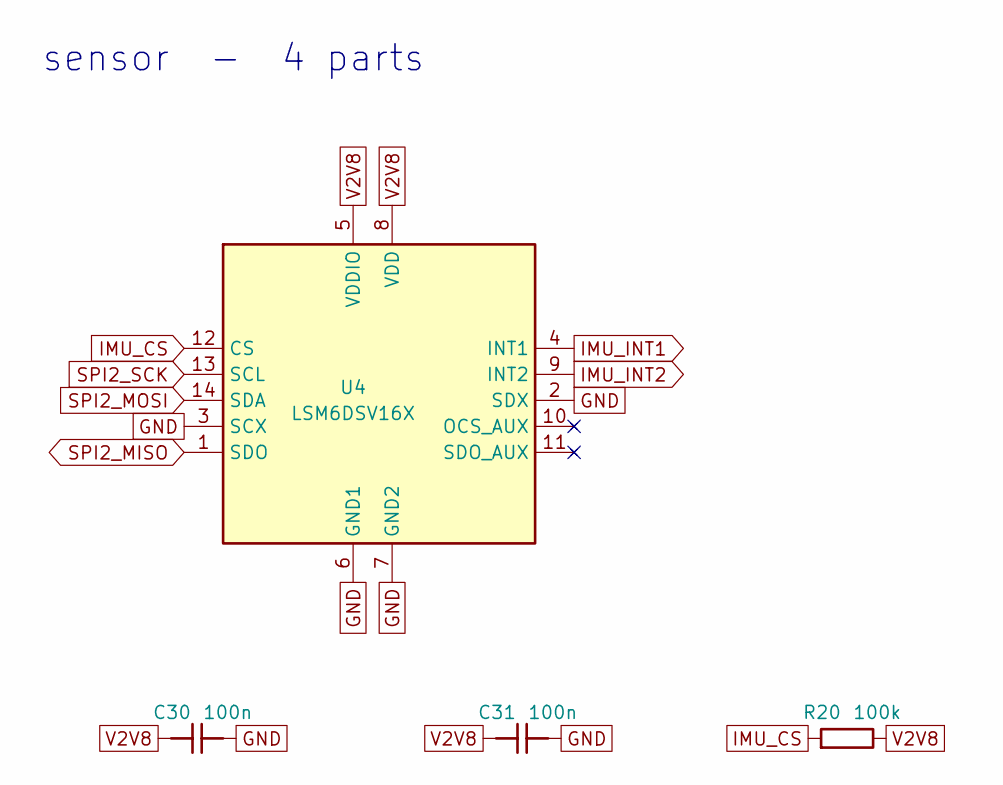
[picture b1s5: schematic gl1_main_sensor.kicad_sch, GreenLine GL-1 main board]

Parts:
C30, C31: 100n; C_0402_1005Metric; MPN GRM155R71C104KA88D
R20: 100k; R_0402_1005Metric; MPN RC0402FR-07100KL
U4: LSM6DSV16X; LGA-14_3x2.5mm_P0.5mm_LayoutBorder3x4y; MPN LSM6DSV16XTR

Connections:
GND: C30.2, C31.2, U4.2 (SDX), U4.3 (SCX), U4.6 (GND1), U4.7 (GND2); also elsewhere on the board
IMU_CS: R20.1, U4.12 (CS); also elsewhere on the board
IMU_INT1: U4.4 (INT1); also elsewhere on the board
IMU_INT2: U4.9 (INT2); also elsewhere on the board
SPI2_MISO: U4.1 (SDO); also elsewhere on the board
SPI2_MOSI: U4.14 (SDA); also elsewhere on the board
SPI2_SCK: U4.13 (SCL); also elsewhere on the board
V2V8: C30.1, C31.1, R20.2, U4.5 (VDDIO), U4.8 (VDD); also elsewhere on the board

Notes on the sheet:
sensor - 4 parts

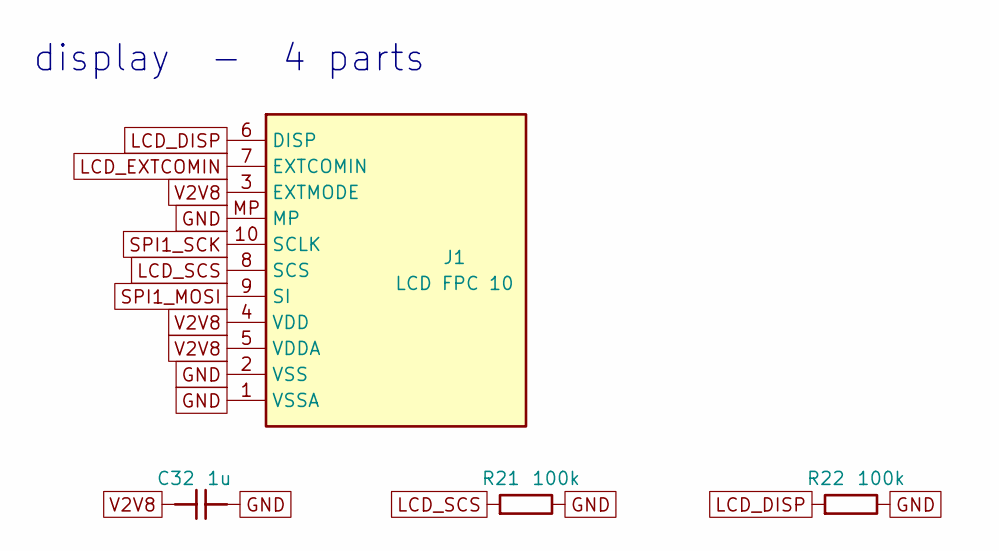
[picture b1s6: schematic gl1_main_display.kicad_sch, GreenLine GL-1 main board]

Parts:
C32: 1u; C_0402_1005Metric; MPN CL05A105KP5NNNC
J1: LCD FPC 10; Hirose_FH12-10S-0.5SH_1x10-1MP_P0.50mm_Horizontal; MPN FH12A-10S-0.5SH(55)
R21, R22: 100k; R_0402_1005Metric; MPN RC0402FR-07100KL

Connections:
GND: C32.2, J1.1 (VSSA), J1.2 (VSS), J1.MP, R21.2, R22.2; also elsewhere on the board
LCD_DISP: J1.6 (DISP), R22.1; also elsewhere on the board
LCD_EXTCOMIN: J1.7 (EXTCOMIN); also elsewhere on the board
LCD_SCS: J1.8 (SCS), R21.1; also elsewhere on the board
SPI1_MOSI: J1.9 (SI); also elsewhere on the board
SPI1_SCK: J1.10 (SCLK); also elsewhere on the board
V2V8: C32.1, J1.3 (EXTMODE), J1.4 (VDD), J1.5 (VDDA); also elsewhere on the board

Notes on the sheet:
display - 4 parts

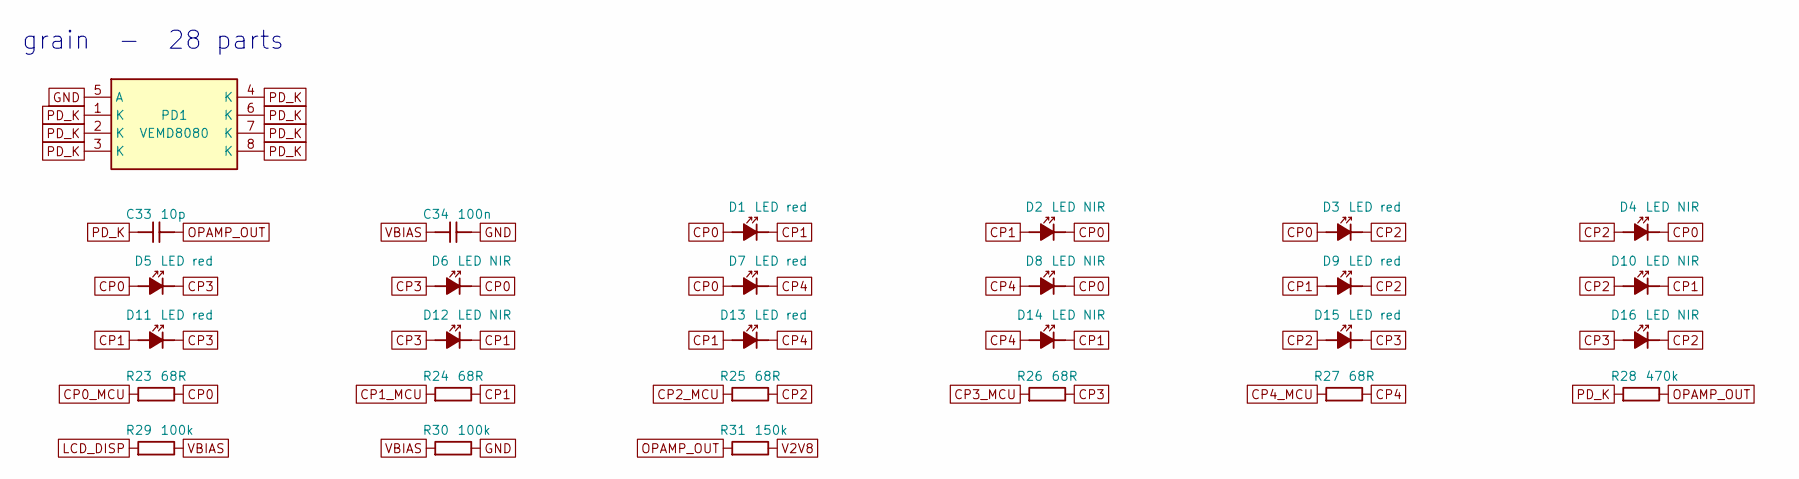
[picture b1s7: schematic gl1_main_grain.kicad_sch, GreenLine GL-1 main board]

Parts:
C33: 10p; C_0402_1005Metric; MPN GRM1555C1H100JA01D
C34: 100n; C_0402_1005Metric; MPN GRM155R71C104KA88D
D1, D3, D5, D7, D9, D11, D13, D15: LED red; LED_0402_1005Metric; MPN VLMS1500-GS08
D2, D4, D6, D8, D10, D12, D14, D16: LED NIR; LED_0402_1005Metric; MPN SFH 4053B
PD1: VEMD8080; VEMD8080_4.8x2.5mm_PROVISIONAL; MPN VEMD8080
R23, R24, R25, R26, R27: 68R; R_0402_1005Metric; MPN RC0402FR-0768RL
R28: 470k; R_0402_1005Metric; MPN RC0402FR-07470KL
R29, R30: 100k; R_0402_1005Metric; MPN RC0402FR-07100KL
R31: 150k; R_0402_1005Metric; MPN RC0402FR-07150KL

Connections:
CP0: D1.2 (A), D2.1 (K), D3.2 (A), D4.1 (K), D5.2 (A), D6.1 (K), D7.2 (A), D8.1 (K), R23.2
CP0_MCU: R23.1; also elsewhere on the board
CP1: D1.1 (K), D2.2 (A), D9.2 (A), D10.1 (K), D11.2 (A), D12.1 (K), D13.2 (A), D14.1 (K), R24.2
CP1_MCU: R24.1; also elsewhere on the board
CP2: D3.1 (K), D4.2 (A), D9.1 (K), D10.2 (A), D15.2 (A), D16.1 (K), R25.2
CP2_MCU: R25.1; also elsewhere on the board
CP3: D5.1 (K), D6.2 (A), D11.1 (K), D12.2 (A), D15.1 (K), D16.2 (A), R26.2
CP3_MCU: R26.1; also elsewhere on the board
CP4: D7.1 (K), D8.2 (A), D13.1 (K), D14.2 (A), R27.2
CP4_MCU: R27.1; also elsewhere on the board
GND: C34.2, PD1.5 (A), R30.2; also elsewhere on the board
LCD_DISP: R29.1; also elsewhere on the board
OPAMP_OUT: C33.2, R28.2, R31.1; also elsewhere on the board
PD_K: C33.1, PD1.1 (K), PD1.2 (K), PD1.3 (K), PD1.4 (K), PD1.6 (K), PD1.7 (K), PD1.8 (K), R28.1; also elsewhere on the board
V2V8: R31.2; also elsewhere on the board
VBIAS: C34.1, R29.2, R30.1; also elsewhere on the board

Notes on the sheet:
grain - 28 parts

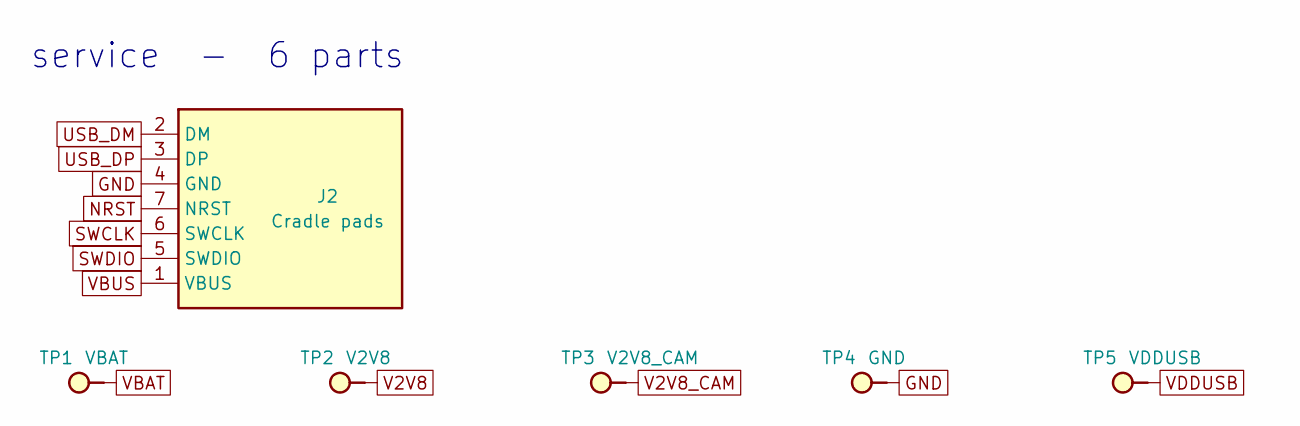
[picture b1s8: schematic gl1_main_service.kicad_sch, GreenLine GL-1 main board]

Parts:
J2: Cradle pads; ContactRow_7x1.8mm_P2.54
TP1: VBAT; TestPad_D1mm
TP2: V2V8; TestPad_D1mm
TP3: V2V8_CAM; TestPad_D1mm
TP4: GND; TestPad_D1mm
TP5: VDDUSB; TestPad_D1mm

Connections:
GND: J2.4 (GND), TP4.1; also elsewhere on the board
NRST: J2.7 (NRST); also elsewhere on the board
SWCLK: J2.6 (SWCLK); also elsewhere on the board
SWDIO: J2.5 (SWDIO); also elsewhere on the board
USB_DM: J2.2 (DM); also elsewhere on the board
USB_DP: J2.3 (DP); also elsewhere on the board
V2V8: TP2.1; also elsewhere on the board
V2V8_CAM: TP3.1; also elsewhere on the board
VBAT: TP1.1; also elsewhere on the board
VBUS: J2.1 (VBUS); also elsewhere on the board
VDDUSB: TP5.1; also elsewhere on the board

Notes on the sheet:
service - 6 parts
